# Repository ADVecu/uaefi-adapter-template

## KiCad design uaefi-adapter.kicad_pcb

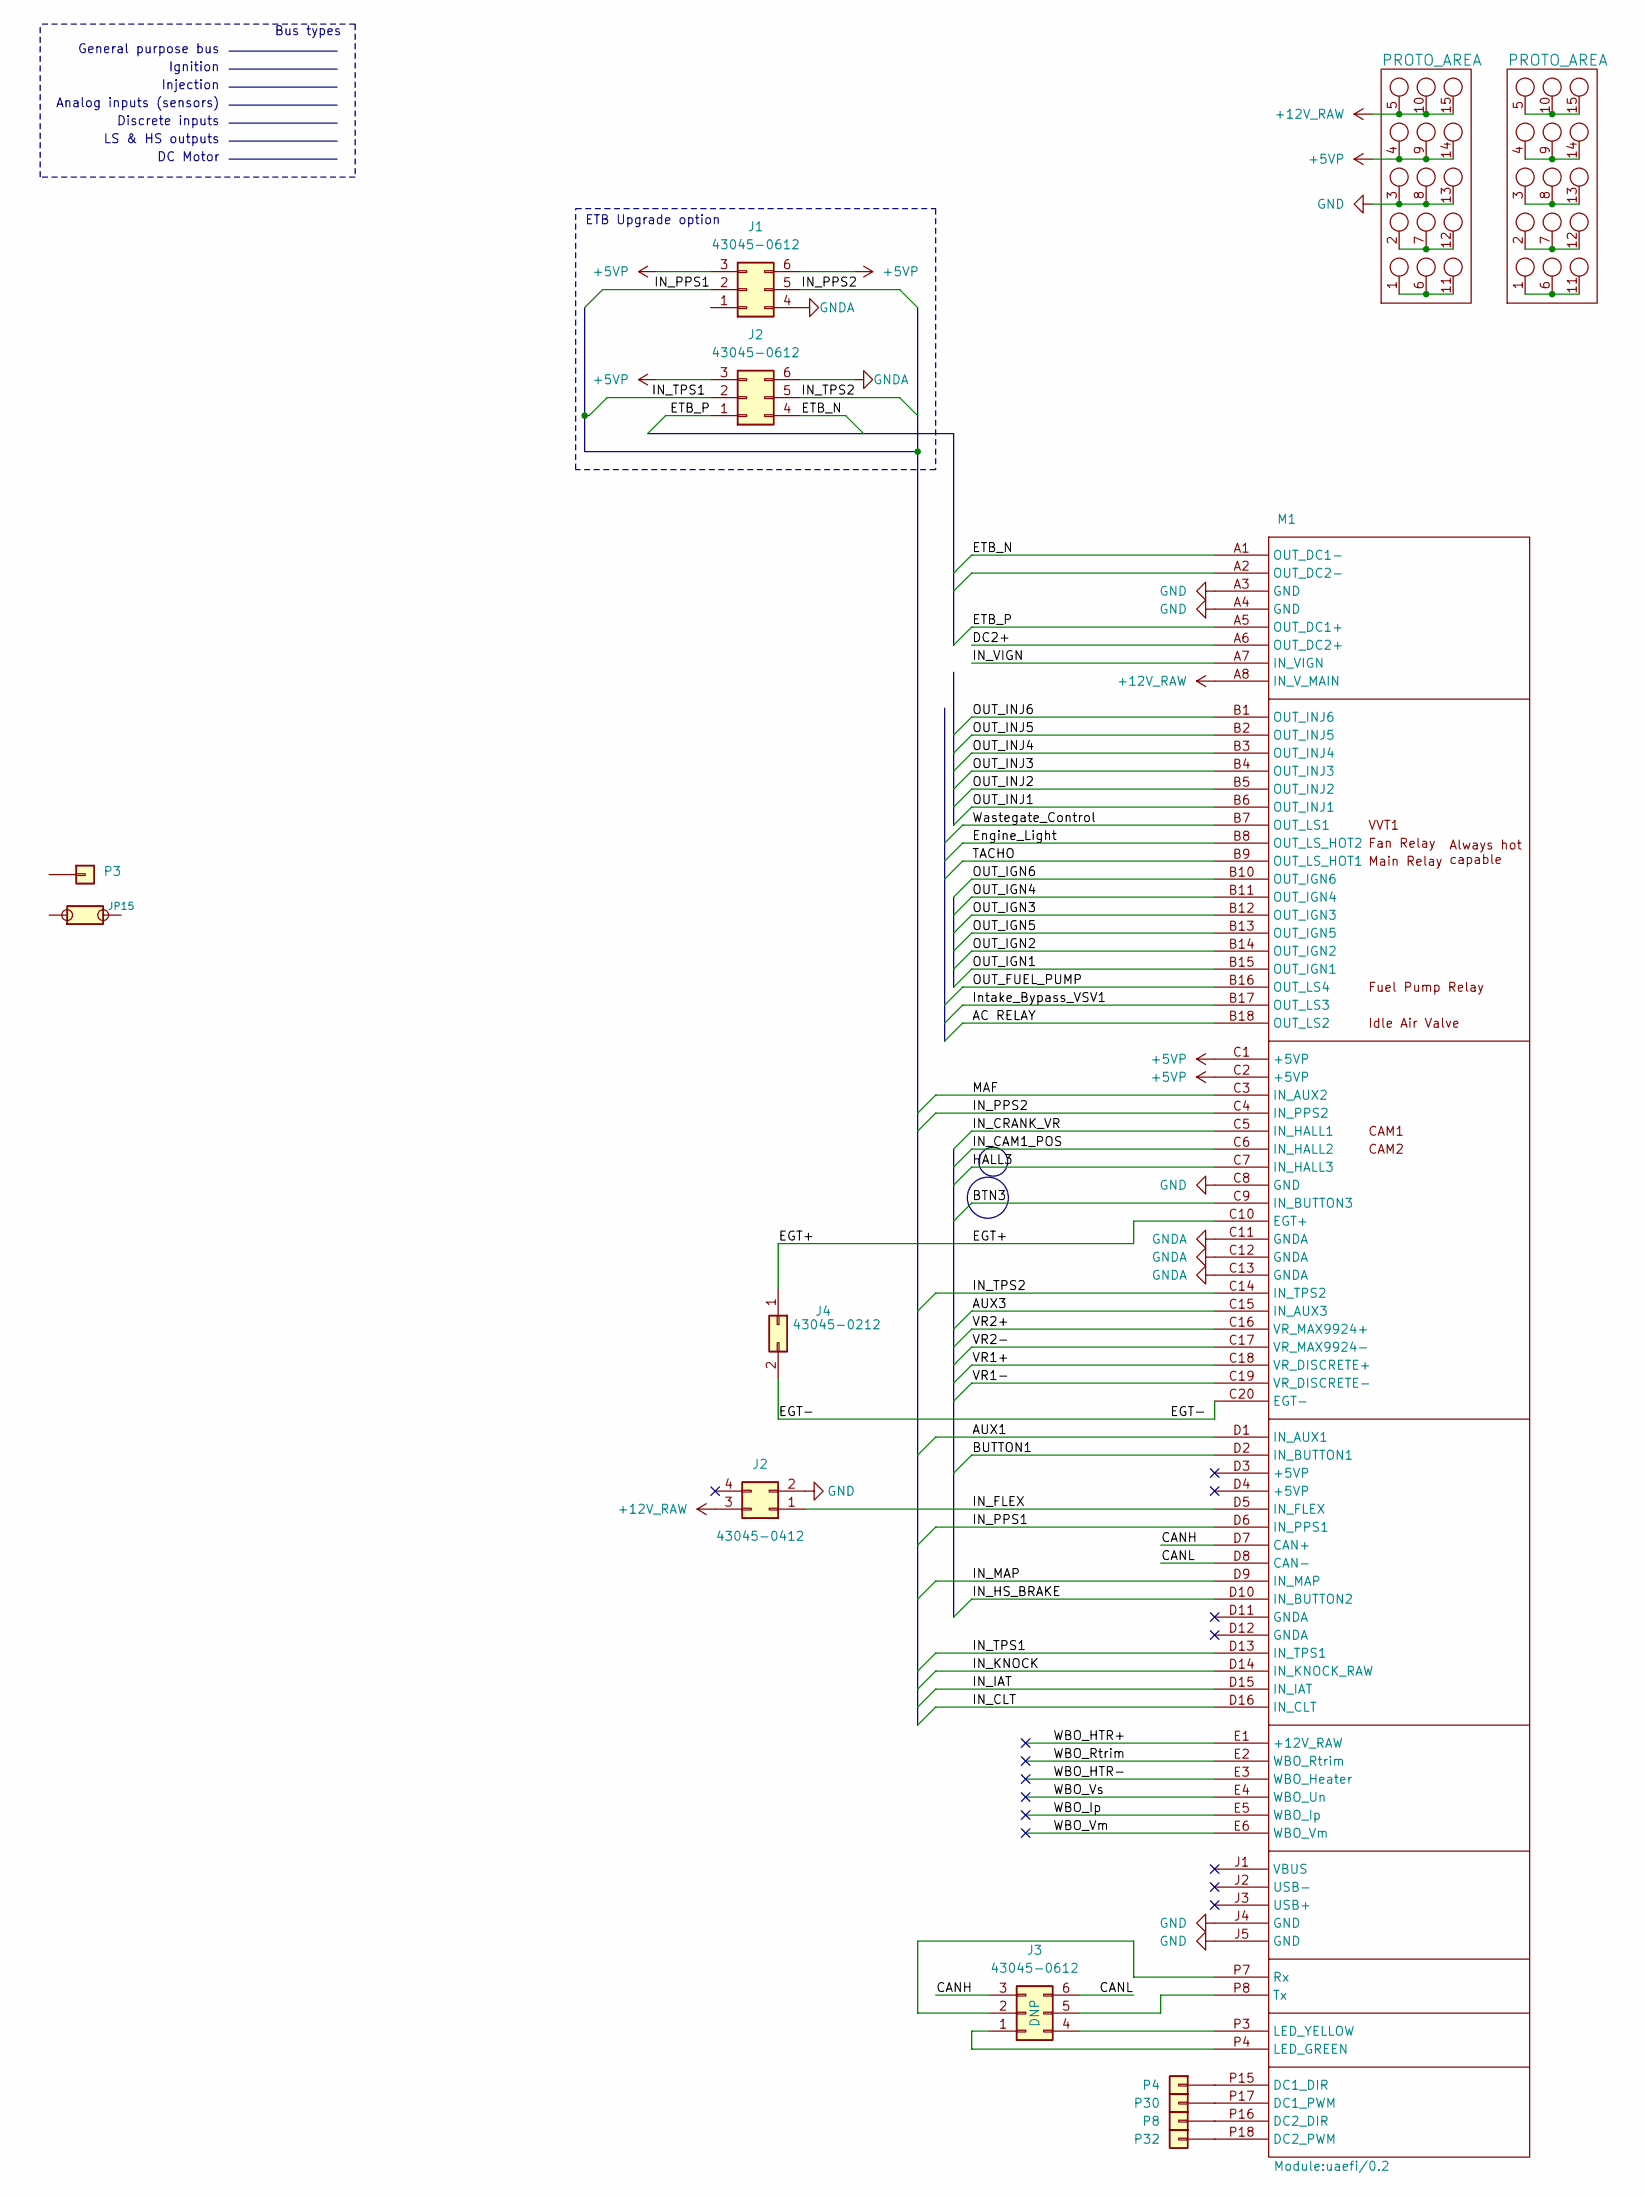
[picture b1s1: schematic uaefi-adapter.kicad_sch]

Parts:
G1, G2: PROTO_AREA
J1: 43045-0612; Molex_Micro-Fit_3.0_43045-0612_2x03_P3.00mm_Vertical; LCSC C234188
J2: 43045-0412; Molex_Micro-Fit_3.0_43045-0412_2x02_P3.00mm_Vertical
J3: 43045-0612; Molex_Micro-Fit_3.0_43045-0612_2x03_P3.00mm_Vertical
J4: 43045-0212; Molex_Micro-Fit_3.0_43045-0212_2x01_P3.00mm_Vertical; LCSC C293362
JP15: Jumper-Pad-Pad; PAD-0805-PAD; LCSC C17477
M1: Module:uaefi/0.2; uaefi
P3, P4, P8, P30, P32: Pad; PAD-TH

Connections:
/AC RELAY: M1.B18 (OUT_LS2)
/AUX1: M1.D1 (IN_AUX1)
/AUX3: M1.C15 (IN_AUX3)
/BTN3: M1.C9 (IN_BUTTON3)
/BUTTON1: M1.D2 (IN_BUTTON1)
/CANH: J3.3, M1.D7 (CAN+)
/CANL: J3.6, M1.D8 (CAN-)
/DC2+: M1.A6 (OUT_DC2+)
/EGT+: J4.1, M1.C10 (EGT+)
/EGT-: J4.2, M1.C20 (EGT-)
/ETB_N: J2.4, M1.A1 (OUT_DC1-)
/Engine_Light: M1.B8 (OUT_LS_HOT2)
/HALL3: M1.C7 (IN_HALL3)
/IN_CAM1_POS: M1.C6 (IN_HALL2)
/IN_CLT: M1.D16 (IN_CLT)
/IN_CRANK_VR: M1.C5 (IN_HALL1)
/IN_HS_BRAKE: M1.D10 (IN_BUTTON2)
/IN_IAT: M1.D15 (IN_IAT)
/IN_KNOCK: M1.D14 (IN_KNOCK_RAW)
/IN_MAP: M1.D9 (IN_MAP)
/IN_PPS1: J1.2, M1.D6 (IN_PPS1)
/IN_PPS2: J1.5, M1.C4 (IN_PPS2)
/IN_TPS2: J2.5, M1.C14 (IN_TPS2)
/IN_VIGN: M1.A7 (IN_VIGN)
/Intake_Bypass_VSV1: M1.B17 (OUT_LS3)
/MAF: M1.C3 (IN_AUX2)
/OUT_FUEL_PUMP: M1.B16 (OUT_LS4)
/OUT_IGN1: M1.B15 (OUT_IGN1)
/OUT_IGN2: M1.B14 (OUT_IGN2)
/OUT_IGN3: M1.B12 (OUT_IGN3)
/OUT_IGN4: M1.B11 (OUT_IGN4)
/OUT_IGN5: M1.B13 (OUT_IGN5)
/OUT_IGN6: M1.B10 (OUT_IGN6)
/OUT_INJ1: M1.B6 (OUT_INJ1)
/OUT_INJ2: M1.B5 (OUT_INJ2)
/OUT_INJ3: M1.B4 (OUT_INJ3)
/OUT_INJ4: M1.B3 (OUT_INJ4)
/OUT_INJ5: M1.B2 (OUT_INJ5)
/OUT_INJ6: M1.B1 (OUT_INJ6)
/TACHO: M1.B9 (OUT_LS_HOT1)
/VR1+: M1.C18 (VR_DISCRETE+)
/VR1-: M1.C19 (VR_DISCRETE-)
/VR2+: M1.C16 (VR_MAX9924+)
/VR2-: M1.C17 (VR_MAX9924-)
/WBO_HTR+: M1.E1 (+12V_RAW)
/WBO_HTR-: M1.E3 (WBO_Heater)
/WBO_Ip: M1.E5 (WBO_Ip)
/WBO_Rtrim: M1.E2 (WBO_Rtrim)
/WBO_Vm: M1.E6 (WBO_Vm)
/WBO_Vs: M1.E4 (WBO_Un)
/Wastegate_Control: M1.B7 (OUT_LS1)
GNDA: J1.4, J2.6, M1.C11 (GNDA), M1.C12 (GNDA), M1.C13 (GNDA)
unnamed: G1.1, G1.6, G1.11
unnamed: G1.2, G1.7, G1.12
unnamed: G2.1, G2.6, G2.11
unnamed: G2.5, G2.10, G2.15
unnamed: G2.2, G2.7, G2.12
unnamed: G2.3, G2.8, G2.13
unnamed: G2.4, G2.9, G2.14
unnamed: J3.1, M1.P4 (LED_GREEN)
unnamed: J3.2, M1.P7 (Rx)
unnamed: J3.4, M1.P3 (LED_YELLOW)
unnamed: J3.5, M1.P8 (Tx)
unnamed: M1.P15 (DC1_DIR), P4.1
unnamed: M1.P17 (DC1_PWM), P30.1
unnamed: M1.P16 (DC2_DIR), P8.1
unnamed: M1.P18 (DC2_PWM), P32.1

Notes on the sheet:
DC Motor
LS & HS outputs
Ignition
Bus types
General purpose bus
ETB Upgrade option
Analog inputs (sensors)
Injection
Discrete inputs

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
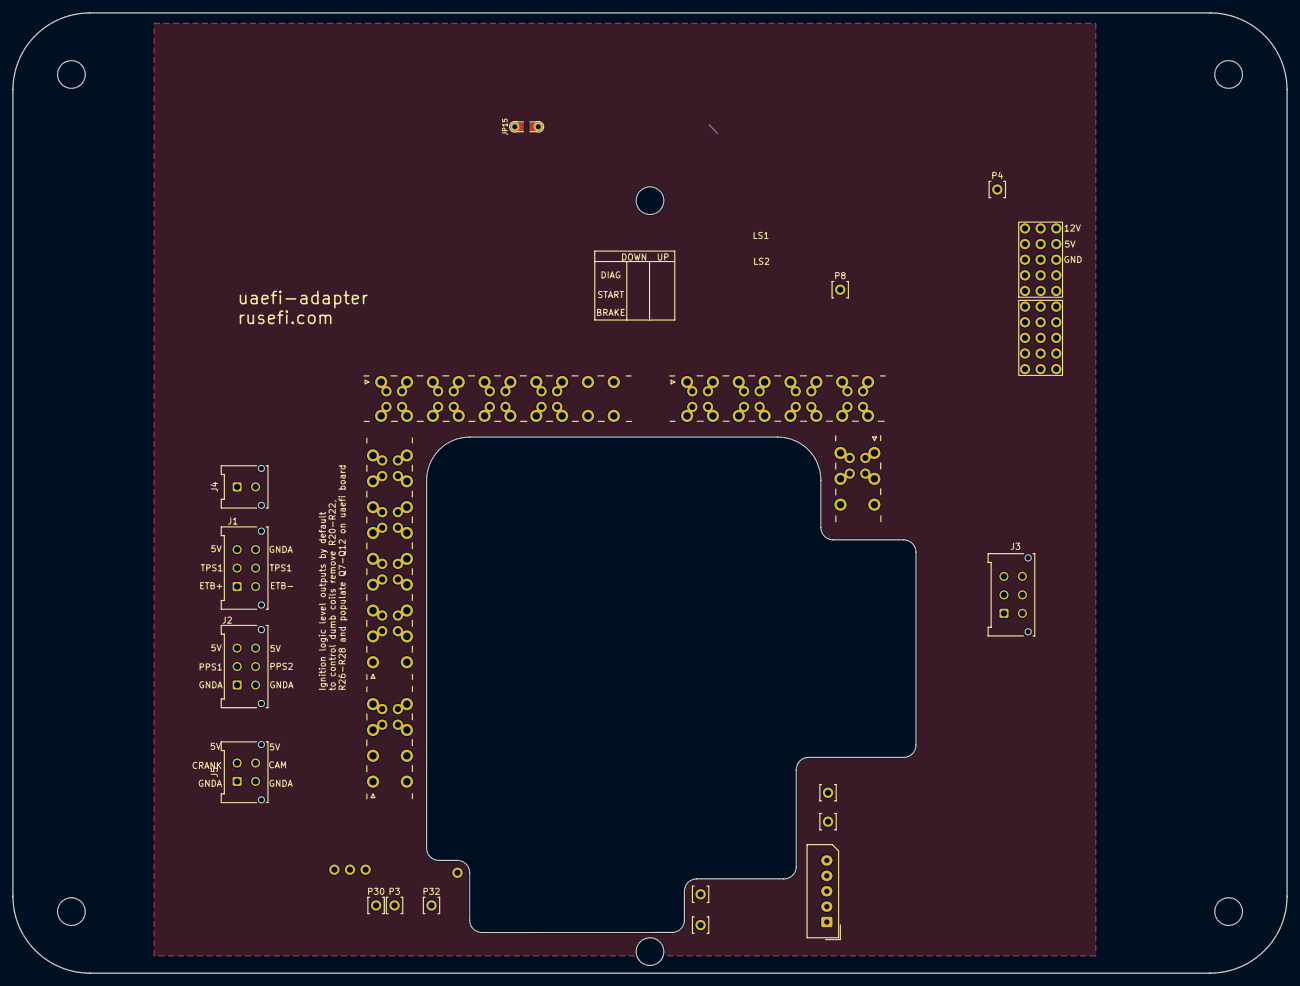
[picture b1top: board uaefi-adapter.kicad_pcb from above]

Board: 2 copper layers, 207.0 x 156.0 mm, 14 parts (0 on the bottom side), 30 nets.

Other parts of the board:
J5: 43045-0412; Molex_Micro-Fit_3.0_43045-0412_2x02_P3.00mm_Vertical

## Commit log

2024-01-18 progress
2024-01-18 GHA says update kicad6-libraries
2024-01-22 manual invocation
2024-02-03 with hellen
2024-02-03 hellen-one cron
2024-02-05 GHA says update hellen-one
